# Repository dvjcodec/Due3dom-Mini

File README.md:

# DUE3DOM MINI

Modular 3D printer driver working as a shield for 32-bit ARM based Arduino DUE.

## Features:
* 20A channel for bed heating (20A fuse) with own power socket
* 10A channel for head heating (10A fuse) with own power socket
* up to 4 external A4988 compatible stepstick drivers (more on expansion port); jumper based step switching
* high current connectors for all power and driver sockets
* input for 4 thermistors (1x onboard; 3x external)
* PWM output for 3 fans
* 4-pin output for board cooling fan driven with signal based on onboard thermistor

## Connections

### Connecting LCD
* EXP1 on DUE3DOM to be connected with EXP2 on SmartController
* EXP2 on DUE3DOM to be connected with EXP1 on SmartController

### Stepstick drivers, motors and other peripherials

## Issues

First board revision (A) needs two manual fixes:
* protection diode [#1](/../../issues/1)
* power on reset capacitor [#2](/../../issues/2)

## Firmware

Supported by official firmware:
* [Repetier](https://www.repetier.com/firmware/dev/index.php)
* [Marlin](https://github.com/esenapaj/Marlin)

## Support
* [Official Website [PL]](http://www.due3dom.pl/)
* [Forum thread [PL/EN]](http://www.fabrykator.pl/board/viewtopic.php?f=12&t=242)

## Where to buy?

* [Seaside Customs](http://fabrykator.pl/seasidecustoms/due3dom-elektronika-32bit-dla-drukarek-3d/)
* Contact: [@dvjcodec](https://github.com/dvjcodec/)

## Demo

## License

[CC BY-NC 3.0](https://creativecommons.org/licenses/by-nc/3.0/)

## Authors

Krzysztof @ Seaside Customs

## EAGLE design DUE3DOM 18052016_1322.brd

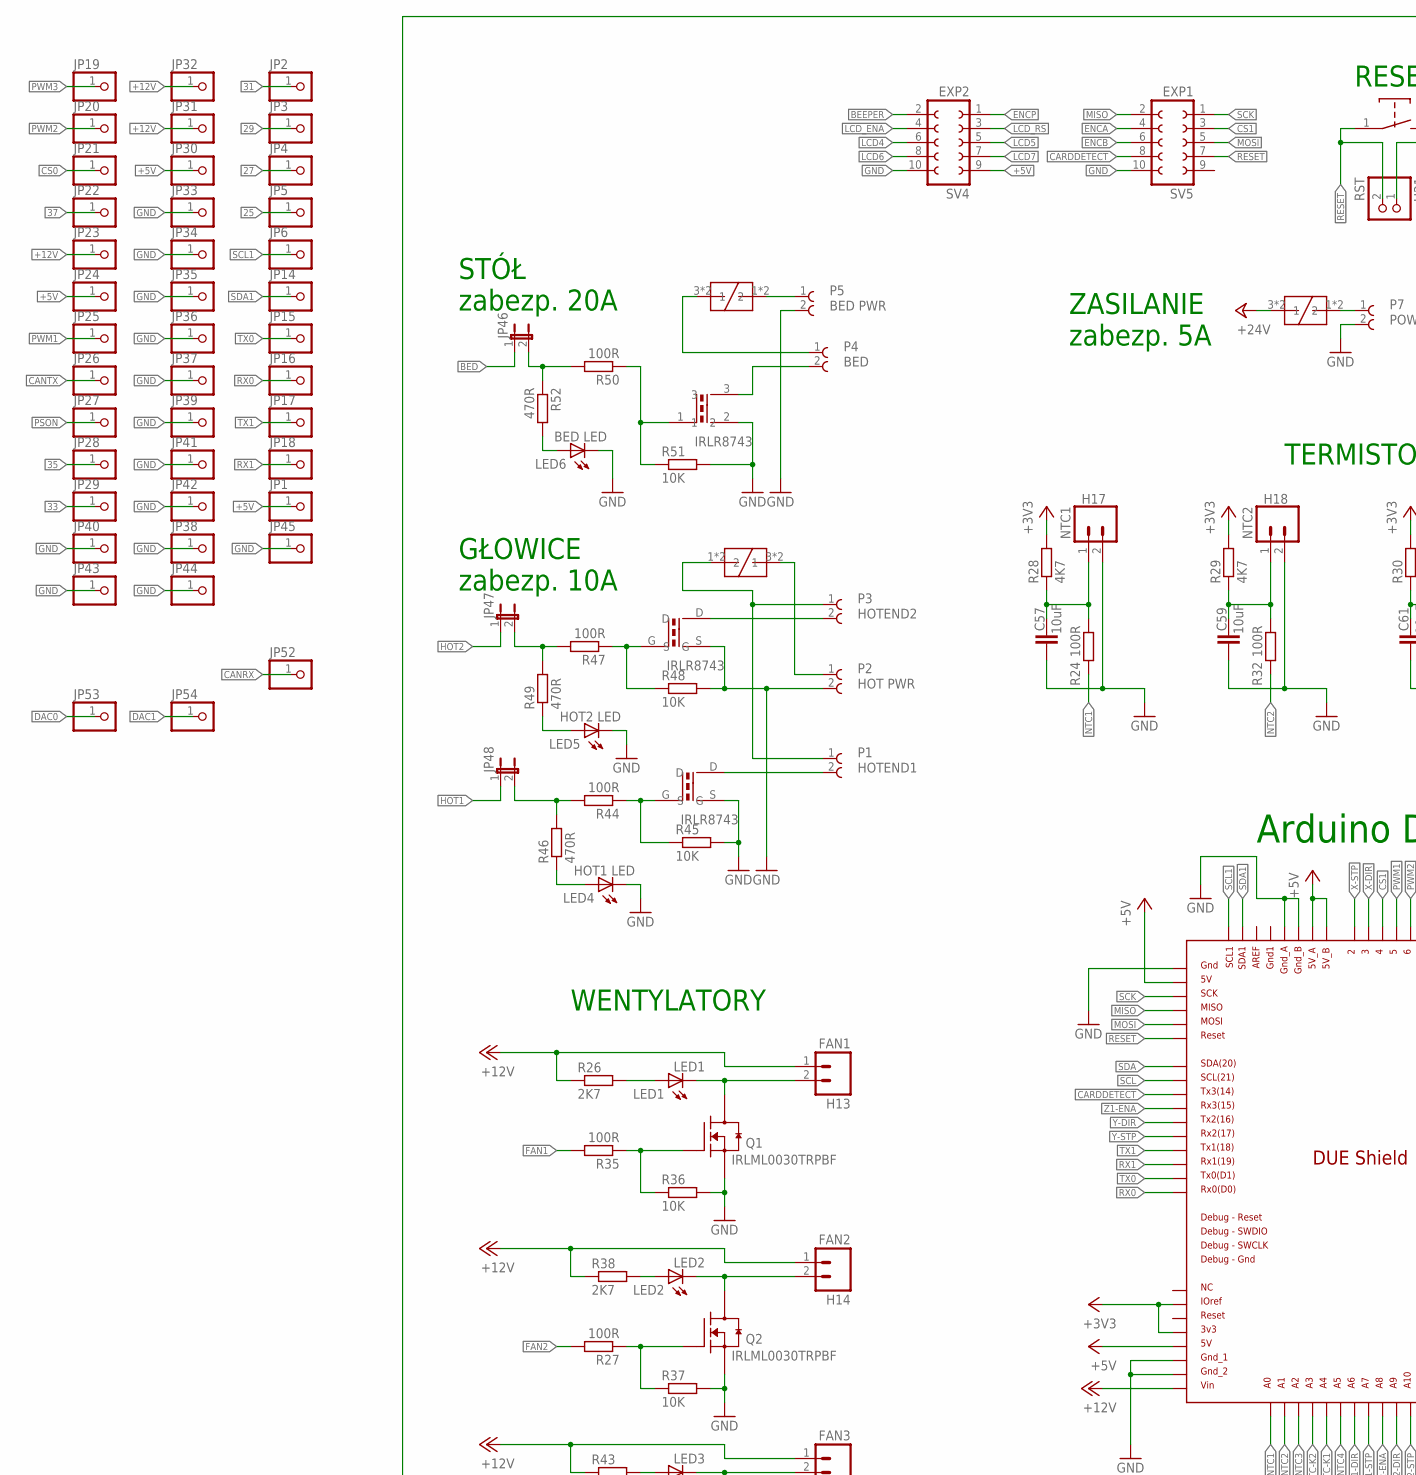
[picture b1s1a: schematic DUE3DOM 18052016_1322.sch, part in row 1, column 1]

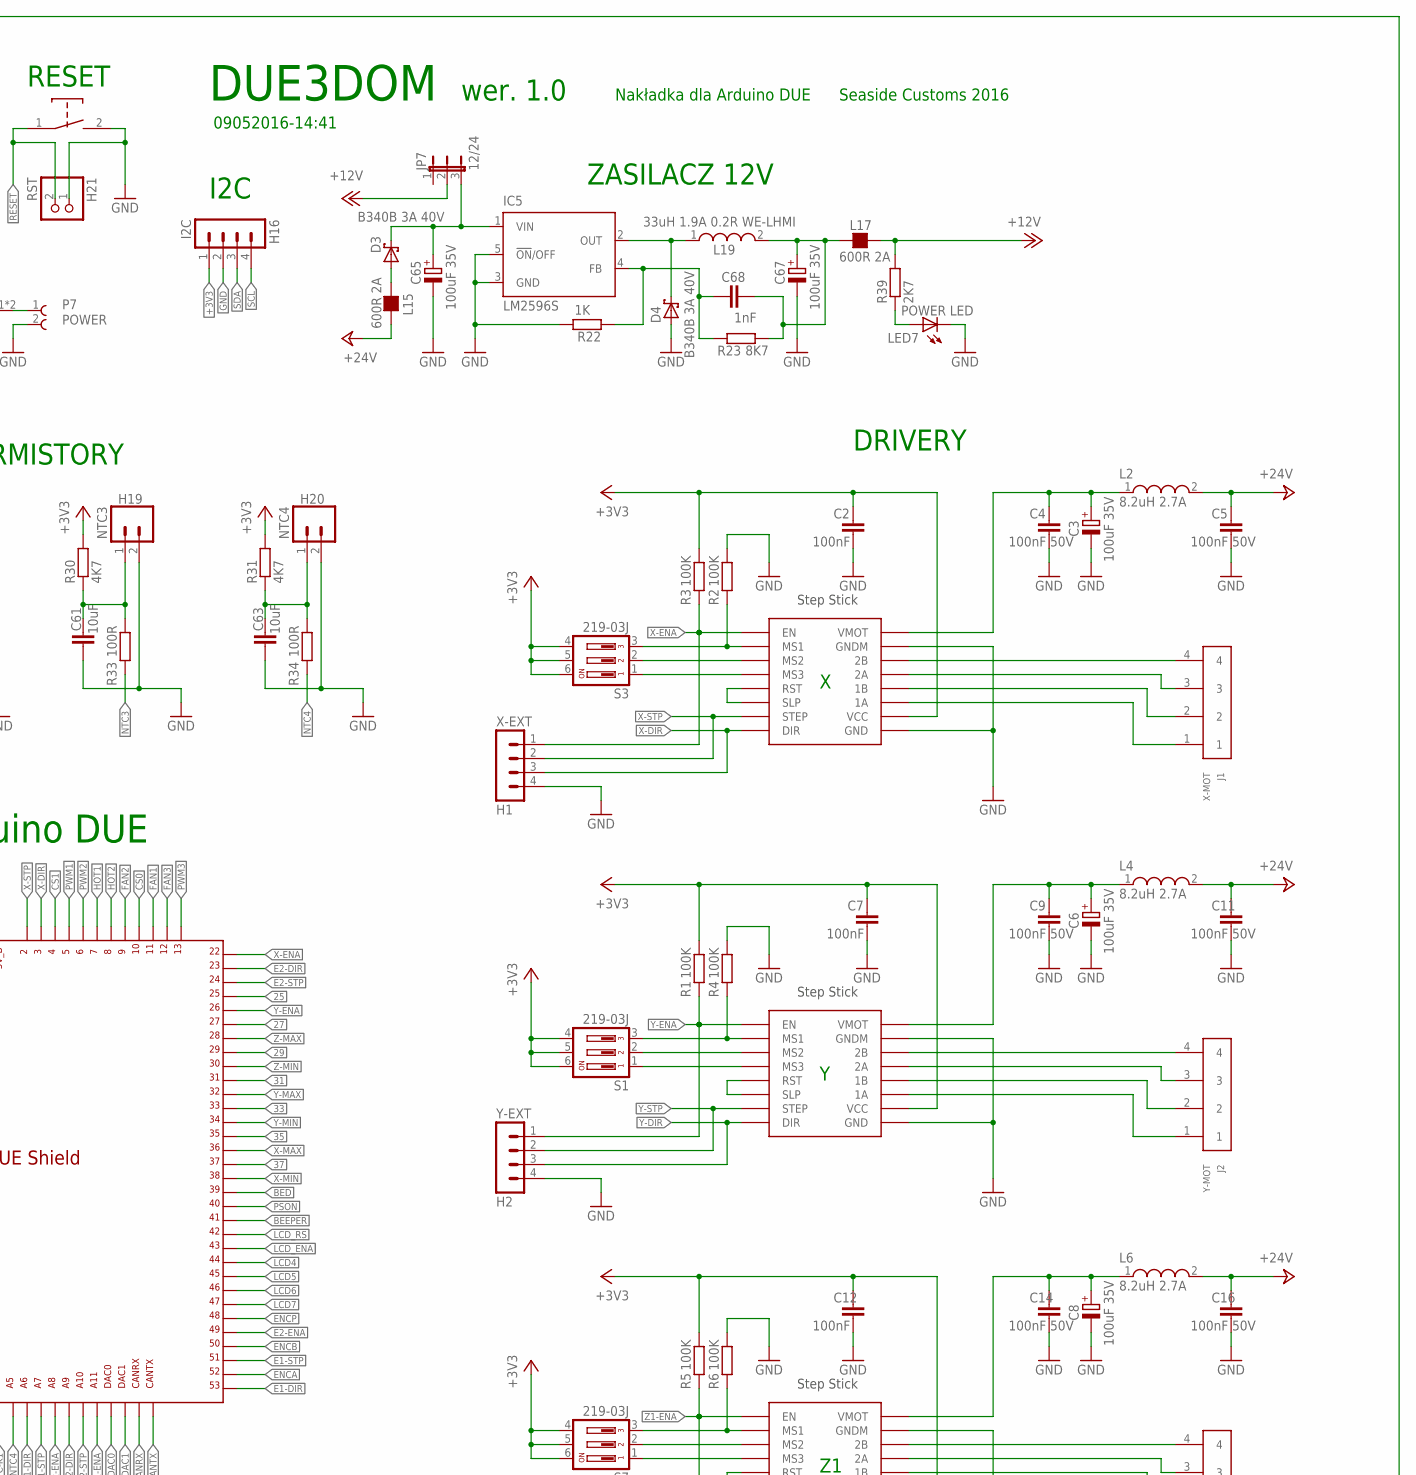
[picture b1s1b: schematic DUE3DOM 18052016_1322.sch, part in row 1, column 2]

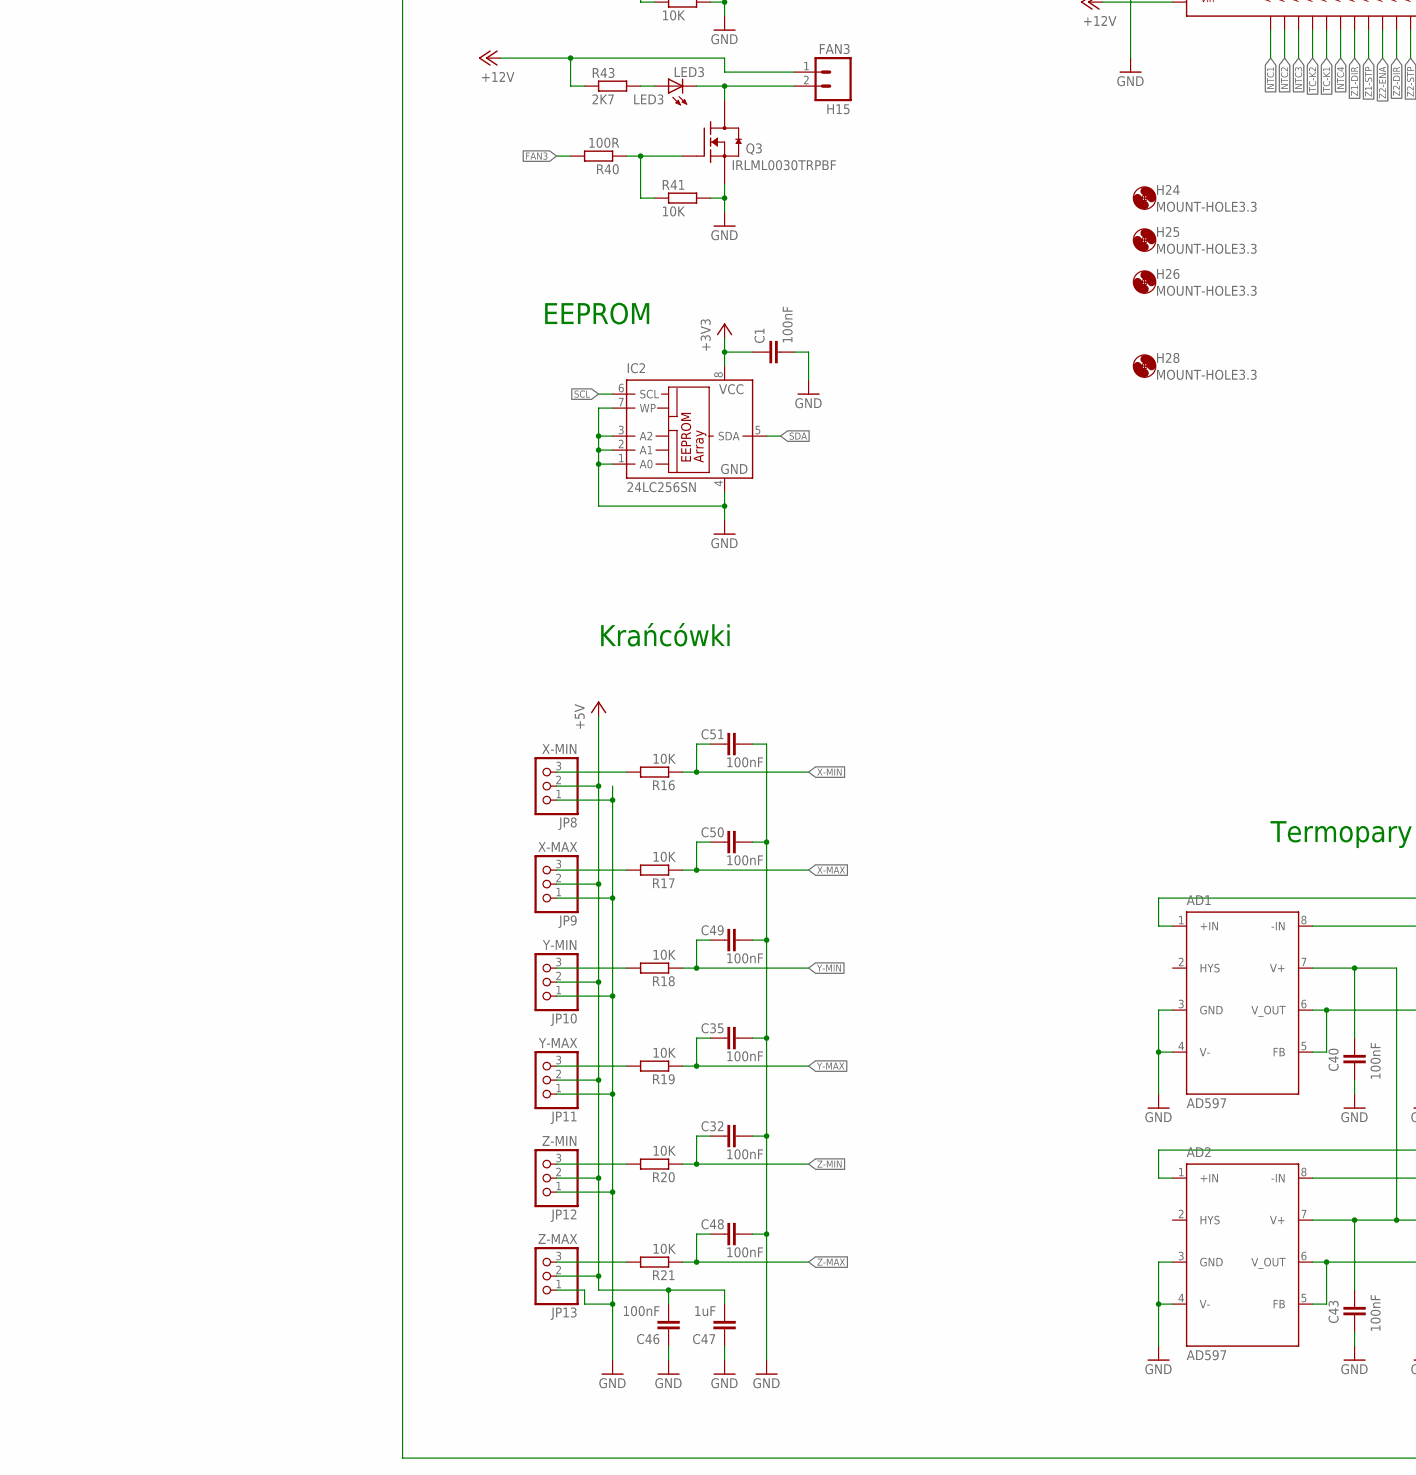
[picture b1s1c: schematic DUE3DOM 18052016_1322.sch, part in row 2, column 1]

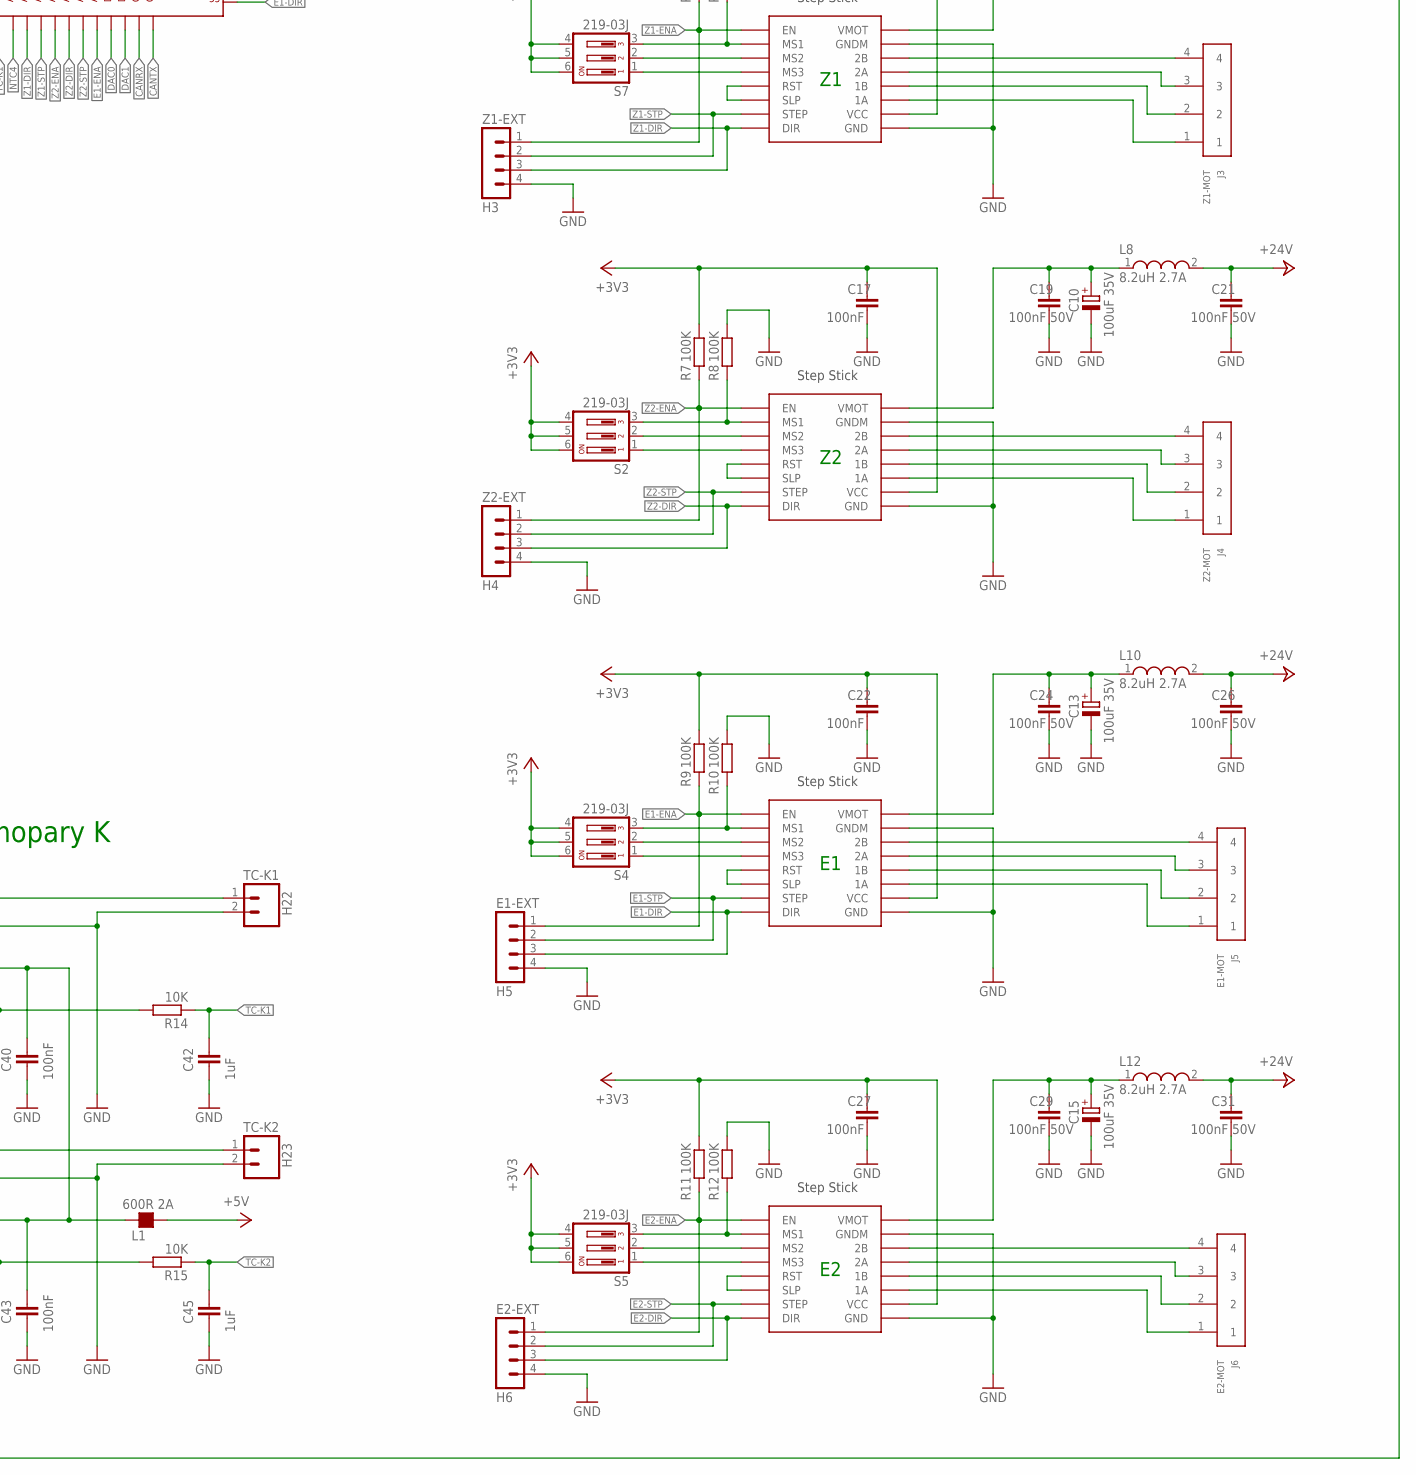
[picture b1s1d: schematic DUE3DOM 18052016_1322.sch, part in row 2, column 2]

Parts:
AD1, AD2: AD597; SO8
C1, C2, C7, C12, C17, C22, C27, C32, C35, C40, C43, C46, C48, C49, C50, C51: 100nF; C0805
C3, C6, C8, C10, C13, C15, C65, C67: 100uF 35V; E2,5-6
C4, C5, C9, C11, C14, C16, C19, C21, C24, C26, C29, C31: 100nF 50V; C0805
C42, C45, C47: 1uF; C0805
C57, C59, C61, C63: 10uF; C0805
C68: 1nF; C0805
D3, D4: B340B 3A 40V; SMB
FET1, FET2: DPAK_N-CHANNEL_MOSFET
FET3: IRLR8743; TO263
H1: X-EXT; MA04-1
H2: Y-EXT; MA04-1
H3: Z1-EXT; MA04-1
H4: Z2-EXT; MA04-1
H5: E1-EXT; MA04-1
H6: E2-EXT; MA04-1
H13: FAN1; MOLEX-1X2
H14: FAN2; MOLEX-1X2
H15: FAN3; MOLEX-1X2
H16: I2C; MA04-1
H17: NTC1; MOLEX-1X2
H18: NTC2; MOLEX-1X2
H19: NTC3; MOLEX-1X2
H20: NTC4; MOLEX-1X2
H21: RST; 1X02
H22: TC-K1; MOLEX-1X2
H23: TC-K2; MOLEX-1X2
H24, H25, H26, H28: MOUNT-HOLE3.3; 3,3
IC2: 24LC256SN; SO-08
IC5: LM2596S; TO263-5
J1: X-MOT; 66100411622
J2: Y-MOT; 66100411622
J3: Z1-MOT; 66100411622
J4: Z2-MOT; 66100411622
J5: E1-MOT; 66100411622
J6: E2-MOT; 66100411622
JP1, JP2, JP3, JP4, JP5, JP6, JP14, JP15, JP16, JP17, JP18, JP19, JP20, JP21, JP22, JP23, JP24, JP25, JP26, JP27, JP28, JP29, JP30, JP31, JP32, JP33, JP34, JP35, JP36, JP37, JP38, JP39, JP40, JP41, JP42, JP43, JP44, JP45, JP52, JP53, JP54: PINHD-1X1; 1X01
JP7: 12/24; JP2
JP8: X-MIN; 1X03
JP9: X-MAX; 1X03
JP10: Y-MIN; 1X03
JP11: Y-MAX; 1X03
JP12: Z-MIN; 1X03
JP13: Z-MAX; 1X03
JP46, JP47, JP48: JP1E; JP1
L1, L15, L17: 600R 2A; L1206
L2, L4, L6, L8, L10, L12: 8.2uH 2.7A; WE-PD_7332/7345_PLASTIC_BASE
L19: 33uH 1.9A 0.2R WE-LHMI; WE-LHMI_7030/7050
LED1: LED1; CHIPLED_0805
LED2: LED2; CHIPLED_0805
LED3: LED3; CHIPLED_0805
LED4: HOT1 LED; CHIPLED_0805
LED5: HOT2 LED; CHIPLED_0805
LED6: BED LED; CHIPLED_0805
LED7: POWER LED; CHIPLED_0805
P1: HOTEND1; 691241710002
P2: HOT PWR; 691241710002
P3: HOTEND2; 691241710002
P4: BED; 691241710002
P5: BED PWR; 691241710002
P7: POWER; 691241710002
Q1, Q2, Q3: IRLML0030TRPBF; SOT95P280X135-3N
R1, R2, R3, R4, R5, R6, R7, R8, R9, R10, R11, R12: 100K; R0805
R14, R15, R16, R17, R18, R19, R20, R21, R36, R37, R41, R45, R48, R51: 10K; R0805
R22: 1K; R0805
R23: 8K7; R0805
R24, R27, R32, R33, R34, R35, R40, R44, R47, R50: 100R; R0805
R26, R38, R39, R43: 2K7; R0805
R28, R29, R30, R31: 4K7; R0805
R46, R49, R52: 470R; R0805
RESET: RESET; WIDE_TACT
S1, S2, S3, S4, S5, S7: 219-03J; CTS-219-03J
STEPSTICK-E1, STEPSTICK-E2: STEP-STICK
STEPSTICK-X: STEP-STICK
STEPSTICK-Y: STEP-STICK
STEPSTICK-Z1, STEPSTICK-Z2: STEP-STICK
SV4: EXP2; FE05-2
SV5: EXP1; FE05-2
U$1: DUE(NORMAL)
U$11, U$12, U$13: KEYSTONE_3568

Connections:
25: JP5.1, U$1.25
27: JP4.1, U$1.27
29: JP3.1, U$1.29
31: JP2.1, U$1.31
33: JP29.1, U$1.33
35: JP28.1, U$1.35
37: JP22.1, U$1.37
+3V3: C1.1, C2.1, C7.1, C12.1, C17.1, C22.1, C27.1, H16.1, IC2.8 (VCC), R1.1, R3.1, R5.1, R7.1, R9.1, R11.1, R28.2, R29.2, R30.2, R31.2, S1.4, S1.5, S1.6, S2.4, S2.5, S2.6, S3.4, S3.5, S3.6, S4.4, S4.5, S4.6, S5.4, S5.5, S5.6, S7.4, S7.5, S7.6, STEPSTICK-E1.VDD (VCC), STEPSTICK-E2.VDD (VCC), STEPSTICK-X.VDD (VCC), STEPSTICK-Y.VDD (VCC), STEPSTICK-Z1.VDD (VCC), STEPSTICK-Z2.VDD (VCC), U$1.3V3, U$1.IOREF
+5V: C46.2, C47.2, JP1.1, JP8.2, JP9.2, JP10.2, JP11.2, JP12.2, JP13.2, JP24.1, JP30.1, L1.2, SV4.9, U$1.5V, U$1.5V_A, U$1.5V_B, U$1.GND_ICSP
+12V: H13.1, H14.1, H15.1, JP7.2, JP23.1, JP31.1, JP32.1, L17.2, R26.1, R38.1, R39.2, R43.1, U$1.VIN
+24V: C5.1, C11.1, C16.1, C21.1, C26.1, C31.1, L2.2, L4.2, L6.2, L8.2, L10.2, L12.2, L15.1, U$11.3 (2), U$11.4 (2)
BED: JP46.1, U$1.39
BEEPER: SV4.2, U$1.41
CANRX: JP52.1, U$1.CANRX
CANTX: JP26.1, U$1.CANTX
CARDDETECT: SV5.8, U$1.TX3
CS0: JP21.1, U$1.10
CS1: SV5.3, U$1.4
DAC0: JP53.1, U$1.DAC0
DAC1: JP54.1, U$1.DAC1
E1-DIR: H5.3, STEPSTICK-E1.DIR, U$1.53
E1-ENA: H5.1, R9.2, STEPSTICK-E1.ENABLE (EN), U$1.A11
E1-STP: H5.2, STEPSTICK-E1.STP (STEP), U$1.51
E2-DIR: H6.3, STEPSTICK-E2.DIR, U$1.23
E2-ENA: H6.1, R11.2, STEPSTICK-E2.ENABLE (EN), U$1.49
E2-STP: H6.2, STEPSTICK-E2.STP (STEP), U$1.24
ENCA: SV5.4, U$1.52
ENCB: SV5.6, U$1.50
ENCP: SV4.1, U$1.48
FAN1: R35.2, U$1.11
FAN2: R27.2, U$1.9
FAN3: R40.2, U$1.12
GND: AD1.3 (GND), AD1.4 (V-), AD1.8 (-IN), AD2.3 (GND), AD2.4 (V-), AD2.8 (-IN), C1.2, C2.2, C3.-, C4.2, C5.2, C6.-, C7.2, C8.-, C9.2, C10.-, C11.2, C12.2, C13.-, C14.2, C15.-, C16.2, C17.2, C19.2, C21.2, C22.2, C24.2, C26.2, C27.2, C29.2, C31.2, C32.1, C35.1, C40.2, C42.2, C43.2, C45.2, C46.1, C47.1, C48.1, C49.1, C50.1, C51.1, C57.2, C59.2, C61.2, C63.2, C65.-, C67.-, D4.A, FET1.S, FET2.S, FET3.2 (1), H1.4, H2.4, H3.4, H4.4, H5.4, H6.4, H16.2, H17.2, H18.2, H19.2, H20.2, H21.1, H22.2, H23.2, IC2.1 (A0), IC2.2 (A1), IC2.3 (A2), IC2.4 (GND), IC2.7 (WP), IC5.3 (GND), IC5.5 (!ON!/OFF), JP8.1, JP9.1, JP10.1, JP11.1, JP12.1, JP13.1, JP33.1, JP34.1, JP35.1, JP36.1, JP37.1, JP38.1, JP39.1, JP40.1, JP41.1, JP42.1, JP43.1, JP44.1, JP45.1, LED4.C, LED5.C, LED6.C, LED7.C, P2.2, P5.2, P7.2, Q1.2 (S), Q2.2 (S), Q3.2 (S), R2.1, R4.1, R6.1, R8.1, R10.1, R12.1, R22.1, R36.2, R37.2, R41.2, R45.2, R48.2, R51.2, RESET.2, STEPSTICK-E1.GND (GNDM), STEPSTICK-E1.GND1 (GND), STEPSTICK-E2.GND (GNDM), STEPSTICK-E2.GND1 (GND), STEPSTICK-X.GND (GNDM), STEPSTICK-X.GND1 (GND), STEPSTICK-Y.GND (GNDM), STEPSTICK-Y.GND1 (GND), STEPSTICK-Z1.GND (GNDM), STEPSTICK-Z1.GND1 (GND), STEPSTICK-Z2.GND (GNDM), STEPSTICK-Z2.GND1 (GND), SV4.10, SV5.10, U$1.5V_ICSP, U$1.GND_1, U$1.GND_2, U$1.GND_A, U$1.GND_B
HOT1: JP48.1, U$1.7
HOT2: JP47.1, U$1.8
LCD4: SV4.6, U$1.44
LCD5: SV4.5, U$1.45
LCD6: SV4.8, U$1.46
LCD7: SV4.7, U$1.47
LCD_ENA: SV4.4, U$1.43
LCD_RS: SV4.3, U$1.42
MISO: SV5.2, U$1.MISO_ICSP
MOSI: SV5.5, U$1.MOSI_ICSP
unnamed: S1.2, STEPSTICK-Y.MS2
unnamed: C57.1, H17.1, R24.1, R28.1
unnamed: C61.1, H19.1, R30.1, R33.1
unnamed: C63.1, H20.1, R31.1, R34.1
unnamed: STEPSTICK-X.RESET (RST), STEPSTICK-X.SLEEP (SLP)
unnamed: AD1.7 (V+), AD2.7 (V+), C40.1, C43.1, L1.1
unnamed: P5.1, U$13.1, U$13.2 (1)
unnamed: J1.4, STEPSTICK-X.2B
unnamed: P2.1, U$12.3 (2), U$12.4 (2)
unnamed: R2.2, S3.3, STEPSTICK-X.MS1
unnamed: S3.2, STEPSTICK-X.MS2
unnamed: S3.1, STEPSTICK-X.MS3
unnamed: J1.3, STEPSTICK-X.2A
unnamed: J1.2, STEPSTICK-X.1B
unnamed: J1.1, STEPSTICK-X.1A
unnamed: C59.1, H18.1, R29.1, R32.1
unnamed: C3.+, C4.1, L2.1, STEPSTICK-X.VMOT
unnamed: R4.2, S1.3, STEPSTICK-Y.MS1
unnamed: S1.1, STEPSTICK-Y.MS3
unnamed: S7.2, STEPSTICK-Z1.MS2
unnamed: STEPSTICK-Y.RESET (RST), STEPSTICK-Y.SLEEP (SLP)
unnamed: J2.4, STEPSTICK-Y.2B
unnamed: J2.3, STEPSTICK-Y.2A
unnamed: J2.2, STEPSTICK-Y.1B
unnamed: J2.1, STEPSTICK-Y.1A
unnamed: C6.+, C9.1, L4.1, STEPSTICK-Y.VMOT
unnamed: JP9.3, R17.2
unnamed: JP8.3, R16.2
unnamed: R6.2, S7.3, STEPSTICK-Z1.MS1
unnamed: S7.1, STEPSTICK-Z1.MS3
unnamed: S2.2, STEPSTICK-Z2.MS2
unnamed: STEPSTICK-Z1.RESET (RST), STEPSTICK-Z1.SLEEP (SLP)
unnamed: J3.4, STEPSTICK-Z1.2B
unnamed: J3.3, STEPSTICK-Z1.2A
unnamed: J3.2, STEPSTICK-Z1.1B
unnamed: J3.1, STEPSTICK-Z1.1A
unnamed: C8.+, C14.1, L6.1, STEPSTICK-Z1.VMOT
unnamed: JP11.3, R19.2
unnamed: JP10.3, R18.2
unnamed: R8.2, S2.3, STEPSTICK-Z2.MS1
unnamed: S2.1, STEPSTICK-Z2.MS3
unnamed: S4.2, STEPSTICK-E1.MS2
unnamed: STEPSTICK-Z2.RESET (RST), STEPSTICK-Z2.SLEEP (SLP)
unnamed: J4.4, STEPSTICK-Z2.2B
unnamed: J4.3, STEPSTICK-Z2.2A
unnamed: J4.2, STEPSTICK-Z2.1B
unnamed: J4.1, STEPSTICK-Z2.1A
unnamed: C10.+, C19.1, L8.1, STEPSTICK-Z2.VMOT
unnamed: JP13.3, R21.2
unnamed: JP12.3, R20.2
unnamed: R10.2, S4.3, STEPSTICK-E1.MS1
unnamed: S4.1, STEPSTICK-E1.MS3
unnamed: S5.2, STEPSTICK-E2.MS2
unnamed: STEPSTICK-E1.RESET (RST), STEPSTICK-E1.SLEEP (SLP)
unnamed: J5.4, STEPSTICK-E1.2B
unnamed: J5.3, STEPSTICK-E1.2A
unnamed: J5.2, STEPSTICK-E1.1B
unnamed: J5.1, STEPSTICK-E1.1A
unnamed: C13.+, C24.1, L10.1, STEPSTICK-E1.VMOT
unnamed: S5.1, STEPSTICK-E2.MS3
unnamed: R12.2, S5.3, STEPSTICK-E2.MS1
unnamed: STEPSTICK-E2.RESET (RST), STEPSTICK-E2.SLEEP (SLP)
unnamed: J6.4, STEPSTICK-E2.2B
unnamed: J6.3, STEPSTICK-E2.2A
unnamed: J6.2, STEPSTICK-E2.1B
unnamed: J6.1, STEPSTICK-E2.1A
unnamed: C15.+, C29.1, L12.1, STEPSTICK-E2.VMOT
unnamed: AD1.5 (FB), AD1.6 (V_OUT), R14.2
unnamed: AD2.5 (FB), AD2.6 (V_OUT), R15.2
unnamed: AD1.1 (+IN), H22.1
unnamed: AD2.1 (+IN), H23.1
unnamed: LED5.A, R49.1
unnamed: C68.1, IC5.4 (FB), R22.2, R23.1
unnamed: Q2.1 (G), R27.1, R37.1
unnamed: H14.2, LED2.C, Q2.3 (D)
unnamed: LED2.A, R38.2
unnamed: Q1.1 (G), R35.1, R36.1
unnamed: LED4.A, R46.1
unnamed: LED6.A, R52.2
unnamed: D3.A, L15.2
unnamed: H13.2, LED1.C, Q1.3 (D)
unnamed: LED1.A, R26.2
unnamed: Q3.1 (G), R40.1, R41.1
unnamed: H15.2, LED3.C, Q3.3 (D)
unnamed: LED3.A, R43.2
unnamed: FET1.G, R44.1, R45.1
unnamed: FET1.D, P1.2
unnamed: P1.1, P3.1, U$12.1, U$12.2 (1)
unnamed: FET2.G, R47.1, R48.1
unnamed: FET2.D, P3.2
unnamed: FET3.1 (2), R50.1, R51.1
unnamed: FET3.3, P4.2
unnamed: P4.1, U$13.3 (2), U$13.4 (2)
unnamed: JP48.2, R44.2, R46.2
unnamed: JP47.2, R47.2, R49.2
unnamed: JP46.2, R50.2, R52.1
unnamed: LED7.A, R39.1
unnamed: P7.1, U$11.1, U$11.2 (1)
unnamed: C65.+, D3.C, IC5.1 (VIN), JP7.3
unnamed: D4.C, IC5.2 (OUT), L19.1
NTC1: R24.2, U$1.A0
NTC2: R32.2, U$1.A1
NTC3: R33.2, U$1.A2
NTC4: R34.2, U$1.A5
PSON: JP27.1, U$1.40
PWM1: JP25.1, U$1.5
PWM2: JP20.1, U$1.6
PWM3: JP19.1, U$1.13
RESET: H21.2, RESET.1, SV5.7, U$1.RESET_ICSP
RX0: JP16.1, U$1.RX0
RX1: JP18.1, U$1.RX1
SCK: SV5.1, U$1.SCK_ICSP
SCL: H16.4, IC2.6 (SCL), U$1.SCL
SCL1: JP6.1, U$1.SCL1
SDA: H16.3, IC2.5 (SDA), U$1.SDA
SDA1: JP14.1, U$1.SDA1
SUPP1: C67.+, C68.2, L17.1, L19.2, R23.2
TC-K1: C42.1, R14.1, U$1.A4
TC-K2: C45.1, R15.1, U$1.A3
TX0: JP15.1, U$1.TX0
TX1: JP17.1, U$1.TX1
X-DIR: H1.3, STEPSTICK-X.DIR, U$1.3
X-ENA: H1.1, R3.2, STEPSTICK-X.ENABLE (EN), U$1.22
X-MAX: C50.2, R17.1, U$1.36
X-MIN: C51.2, R16.1, U$1.38
X-STP: H1.2, STEPSTICK-X.STP (STEP), U$1.2
Y-DIR: H2.3, STEPSTICK-Y.DIR, U$1.TX2
Y-ENA: H2.1, R1.2, STEPSTICK-Y.ENABLE (EN), U$1.26
Y-MAX: C35.2, R19.1, U$1.32
Y-MIN: C49.2, R18.1, U$1.34
Y-STP: H2.2, STEPSTICK-Y.STP (STEP), U$1.RX2
Z1-DIR: H3.3, STEPSTICK-Z1.DIR, U$1.A6
Z1-ENA: H3.1, R5.2, STEPSTICK-Z1.ENABLE (EN), U$1.RX3
Z1-STP: H3.2, STEPSTICK-Z1.STP (STEP), U$1.A7
Z2-DIR: H4.3, STEPSTICK-Z2.DIR, U$1.A9
Z2-ENA: H4.1, R7.2, STEPSTICK-Z2.ENABLE (EN), U$1.A8
Z2-STP: H4.2, STEPSTICK-Z2.STP (STEP), U$1.A10
Z-MAX: C48.2, R21.1, U$1.28
Z-MIN: C32.2, R20.1, U$1.30

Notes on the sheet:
DRIVERY
Arduino DUE
EEPROM
Termopary K
Krańcówki
DUE3DOM
wer. 1.0
Nakładka dla Arduino DUE
Seaside Customs 2016
WENTYLATORY
GŁOWICE zabezp. 10A
STÓŁ zabezp. 20A
TERMISTORY
ZASILACZ 12V
I2C
RESET
ZASILANIE zabezp. 5A
09052016-14:41

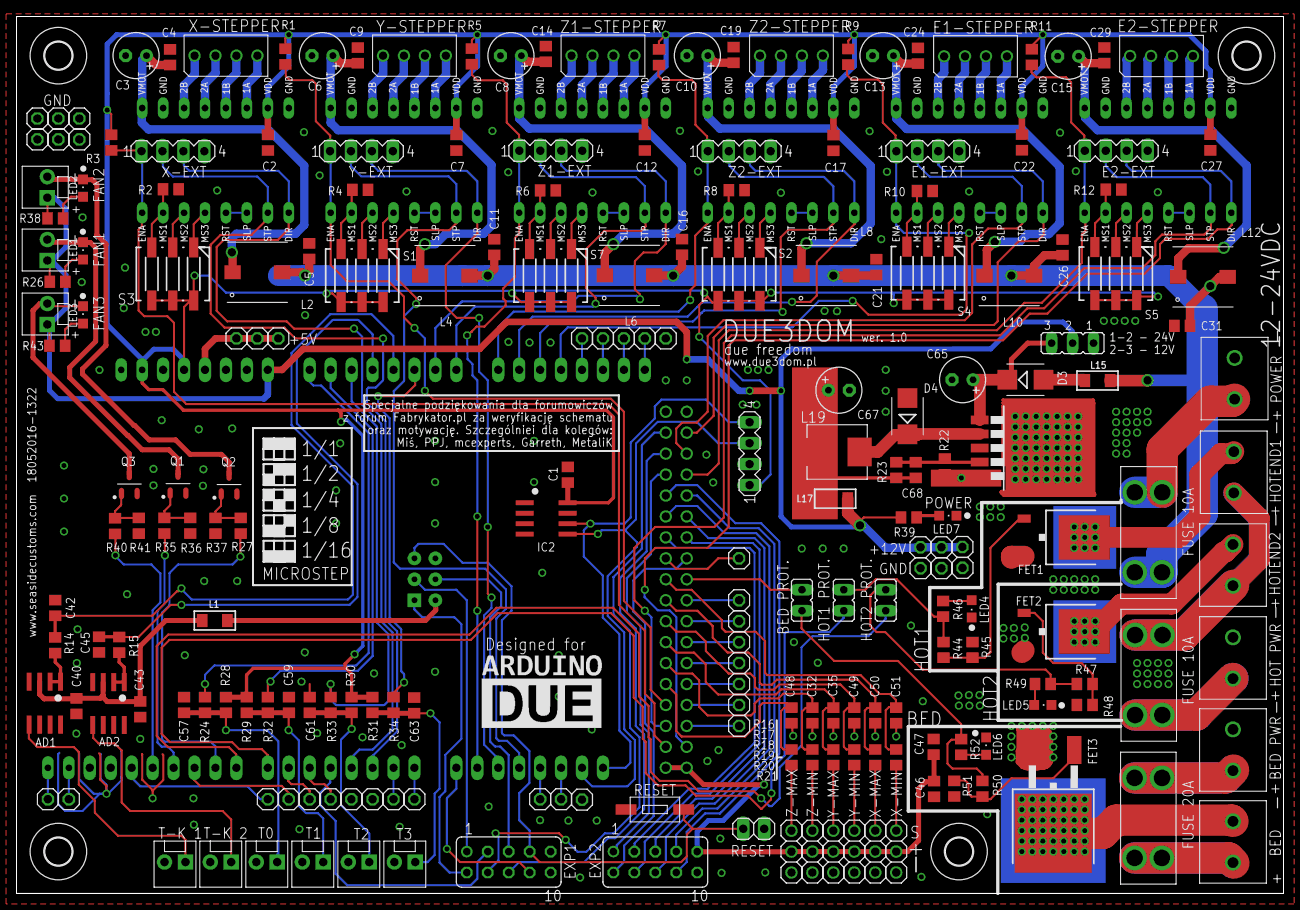
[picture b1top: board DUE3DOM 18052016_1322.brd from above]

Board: 2 copper layers, 153.7 x 106.3 mm, 225 parts (1 on the bottom side), 182 nets.

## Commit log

2017-01-26 Create 3d Model
2017-01-26 Rename 3d Model to 3D-models/readme.md
2017-01-27 Nicer readme, screenshots etc.
2017-01-27 Uncompressed files.

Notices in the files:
parts and their libraries:
Wurth Terminal Block: Copyright: Würth Elektronik
rc-master-smd: Copyright (C) 2007, Bob Starr
